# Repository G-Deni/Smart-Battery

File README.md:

# Smart-Battery
A battery standard used in all of my projects

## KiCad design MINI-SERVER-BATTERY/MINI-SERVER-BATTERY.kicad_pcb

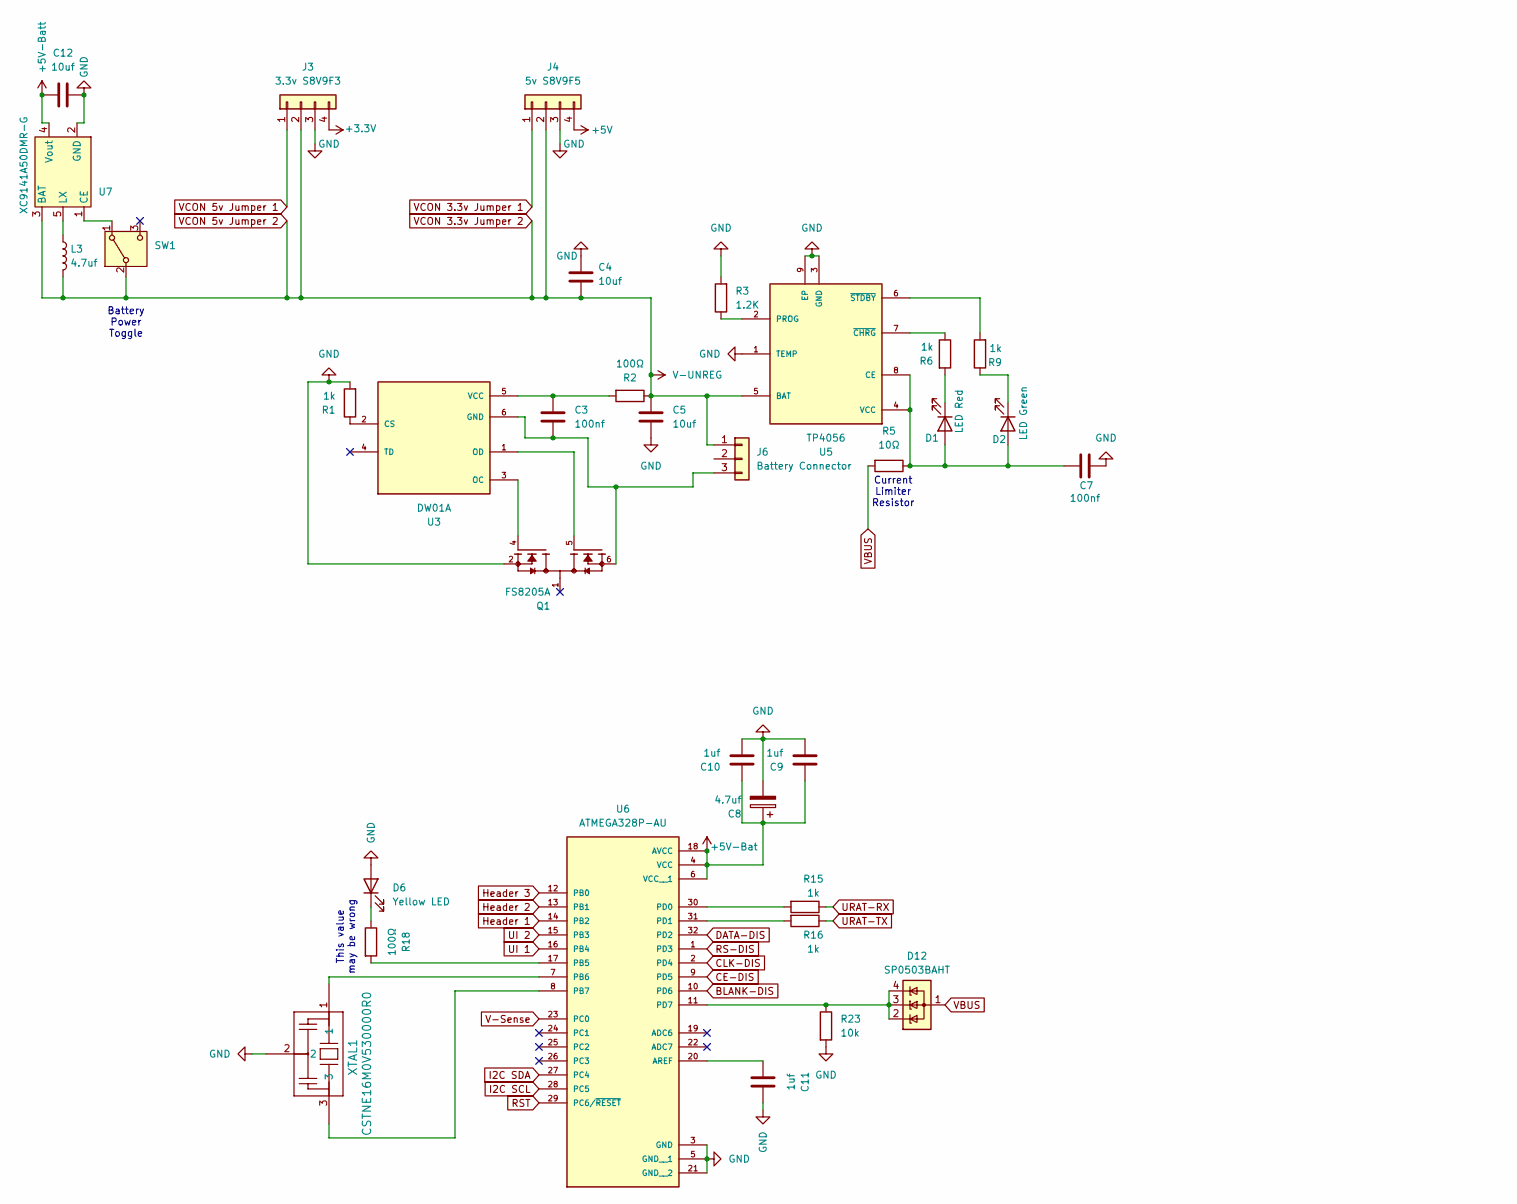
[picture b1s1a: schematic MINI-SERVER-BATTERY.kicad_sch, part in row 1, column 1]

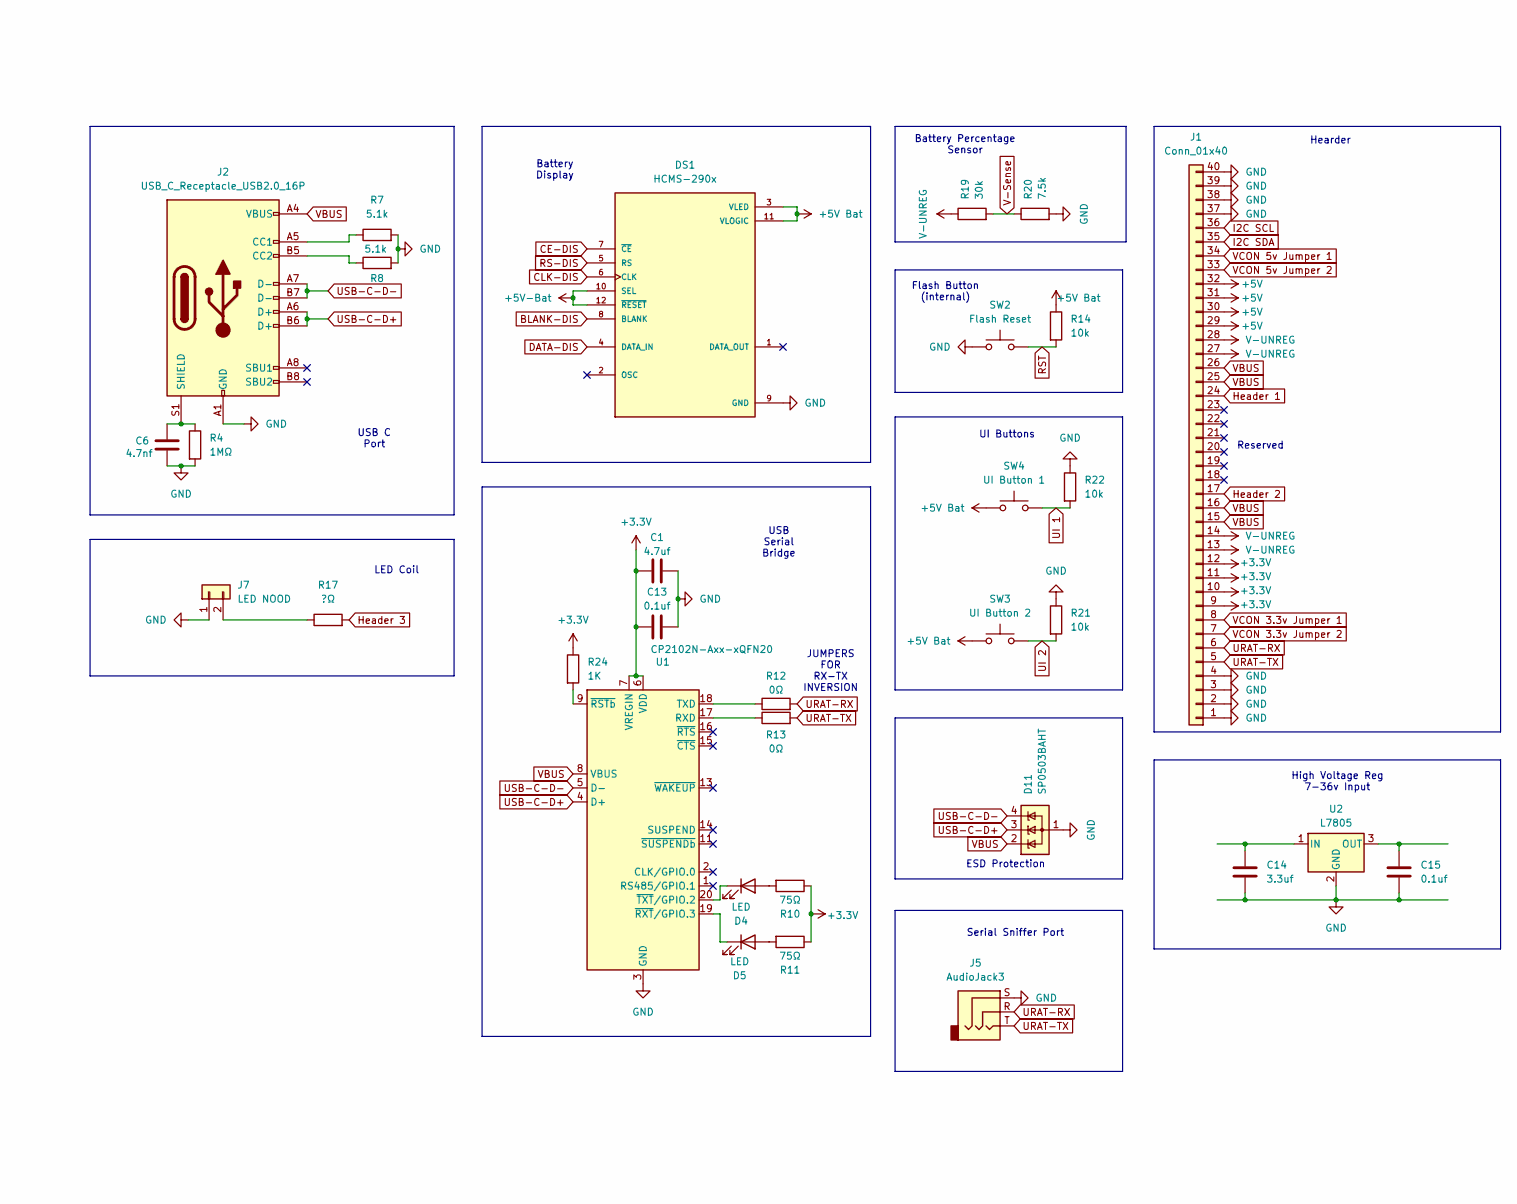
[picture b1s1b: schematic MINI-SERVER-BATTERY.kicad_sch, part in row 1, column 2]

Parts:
C1: 4.7uf; C_0603_1608Metric
C3, C7: 100nf; C_0603_1608Metric
C4, C5, C12: 10uf; C_0603_1608Metric
C6: 4.7nf; C_0603_1608Metric
C8: 4.7uf; C_0603_1608Metric_Pad1.08x0.95mm_HandSolder
C9, C10, C11: 1uf; C_0603_1608Metric_Pad1.08x0.95mm_HandSolder
C13, C15: 0.1uf; C_0603_1608Metric
C14: 3.3uf; C_0603_1608Metric
D1: LED Red; LED_0603_1608Metric
D2: LED Green; LED_0603_1608Metric
D4, D5: LED; LED_0603_1608Metric
D6: Yellow LED; LED_0805_2012Metric
D11, D12: SP0503BAHT; SOT-143
DS1: HCMS-290x; PARTREV N/A
J1: Conn_01x40; Samtec_MECF-20-0_-NP-L-DV_2x20_P1.27mm_Edge
J2: USB_C_Receptacle_USB2.0_16P; TYPE-C-31-M-12
J3: 3.3v S8V9F3; PinSocket_1x04_P2.54mm_Vertical
J4: 5v S8V9F5; PinSocket_1x04_P2.54mm_Vertical
J5: AudioJack3; Jack_3.5mm_CUI_SJ1-3513N_Horizontal
J6: Battery Connector; PinSocket_1x03_P2.54mm_Horizontal
J7: LED NOOD; PinSocket_1x02_P2.54mm_Vertical
L3: 4.7uf; INDPM5752X300N
Q1: FS8205A; SOT-23-6_Handsoldering; PARTREV 1.7
R1, R6, R9: 1k; R_0603_1608Metric
R2: 100Ω; R_0603_1608Metric
R3: 1.2K; R_0603_1608Metric
R4: 1MΩ; R_0603_1608Metric
R5: 10Ω; R_0603_1608Metric
R7, R8: 5.1k; R_0603_1608Metric
R10, R11: 75Ω; R_0603_1608Metric
R12, R13: 0Ω; R_0603_1608Metric
R14, R21, R22, R23: 10k; R_0603_1608Metric_Pad0.98x0.95mm_HandSolder
R15, R16: 1k; R_0603_1608Metric_Pad0.98x0.95mm_HandSolder
R17: ?Ω; R_0603_1608Metric
R18: 100Ω; R_0603_1608Metric_Pad0.98x0.95mm_HandSolder
R19: 30k; R_0603_1608Metric_Pad0.98x0.95mm_HandSolder
R20: 7.5k; R_0603_1608Metric_Pad0.98x0.95mm_HandSolder
R24: 1K; R_0603_1608Metric_Pad0.98x0.95mm_HandSolder
SW1: PCM12SMTR
SW2: Flash Reset; SW_Push_1P1T_NO_CK_KSC7xxJ
SW3: UI Button 2; Vertical Push Button 6_6
SW4: UI Button 1; Vertical Push Button 6_6
U1: CP2102N-Axx-xQFN20; SiliconLabs_QFN-20-1EP_3x3mm_P0.5mm_EP1.8x1.8mm
U2: L7805; TO-220-3_Horizontal_TabDown
U3: DW01A; SOT-23-6_Handsoldering; PARTREV 1.8
U5: TP4056
U6: ATMEGA328P-AU; TQFP-32_7x7mm_P0.8mm; PARTREV 8271A
U7: XC9141A50DMR-G; XC8107AC20MR-G
XTAL1: CSTNE16M0V530000R0

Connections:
+3.3V: C1.1, C13.1, J1.9, J1.10, J1.11, J1.12, J3.4, R10.1, R11.1, R24.1, U1.6 (VDD), U1.7 (VREGIN)
+5V: J1.29, J1.30, J1.31, J1.32, J4.4
+5V Bat: DS1.3 (VLED), DS1.11 (VLOGIC), R14.1, SW3.1, SW4.1
+5V-Bat: C8.1, C9.1, C10.1, DS1.10 (SEL), DS1.12 (~RESET), U6.4 (VCC), U6.6 (VCC__1), U6.18 (AVCC)
+5V-Batt: C12.1, U7.4 (Vout)
BLANK-DIS: DS1.8 (BLANK), U6.10 (PD6)
CE-DIS: DS1.7 (~CE), U6.9 (PD5)
CLK-DIS: DS1.6 (CLK), U6.2 (PD4)
DATA-DIS: DS1.4 (DATA_IN), U6.32 (PD2)
GND: C1.2, C4.2, C5.1, C6.2, C7.1, C8.2, C9.2, C10.2, C11.1, C12.2, C13.2, C14.2, C15.2, D6.2 (A), D11.1 (A), DS1.9 (GND), J1.1, J1.2, J1.3, J1.4, J1.37, J1.38, J1.39, J1.40, J2.A1 (GND), J2.A12 (GND), J2.B1 (GND), J2.B12 (GND), J3.3, J4.3, J5.S, J7.1, Q1.2, Q1.3, R1.2, R3.2, R4.2, R7.2, R8.2, R20.2, R21.1, R22.1, R23.2, SW2.1, U1.3 (GND), U1.12 (GND), U1.21 (GND), U2.2 (GND), U5.1 (TEMP), U5.3 (GND), U5.9 (EP), U6.3 (GND), U6.5 (GND__1), U6.21 (GND__2), U7.2 (GND), XTAL1.2
Header 1: J1.24, U6.14 (PB2)
Header 2: J1.17, U6.13 (PB1)
Header 3: R17.2, U6.12 (PB0)
I2C SCL: J1.36, U6.28 (PC5)
I2C SDA: J1.35, U6.27 (PC4)
unnamed: C7.2, D1.2 (A), D2.2 (A), R5.1, U5.4 (VCC), U5.8 (CE)
unnamed: D1.1 (K), R6.2
unnamed: D2.1 (K), R9.1
unnamed: D4.2 (A), R10.2
unnamed: D4.1 (K), U1.20 (~TXT/GPIO.2)
unnamed: D5.2 (A), R11.2
unnamed: D5.1 (K), U1.19 (~RXT/GPIO.3)
unnamed: D6.1 (K), R18.1
unnamed: J2.A5 (CC1), R7.1
unnamed: J2.B5 (CC2), R8.1
unnamed: C6.1, J2.S1 (SHIELD), R4.1
unnamed: C3.1, J6.3, Q1.6, Q1.7, U3.6 (GND)
unnamed: J7.2, R17.1
unnamed: SW1.1 (A), U7.1 (CE)
unnamed: R13.1, U1.17 (RXD)
unnamed: R12.1, U1.18 (TXD)
unnamed: R24.2, U1.9 (~RSTb)
unnamed: C14.1, U2.1 (IN)
unnamed: C15.1, U2.3 (OUT)
unnamed: R1.1, U3.2 (CS)
unnamed: Q1.4, U3.3 (OC)
unnamed: Q1.5, U3.1 (OD)
unnamed: C3.2, R2.2, U3.5 (VCC)
unnamed: R3.1, U5.2 (PROG)
unnamed: R6.1, U5.7 (~CHRG)
unnamed: R9.2, U5.6 (~STDBY)
unnamed: C11.2, U6.20 (AREF)
unnamed: R18.2, U6.17 (PB5)
unnamed: U6.7 (PB6), XTAL1.1
unnamed: U6.8 (PB7), XTAL1.3
unnamed: R15.2, U6.30 (PD0)
unnamed: R16.2, U6.31 (PD1)
unnamed: D12.2 (K), D12.3 (K), D12.4 (K), R23.1, U6.11 (PD7)
unnamed: L3.1, U7.5 (LX)
RS-DIS: DS1.5 (RS), U6.1 (PD3)
RST: R14.2, SW2.2, U6.29 (PC6/~RESET)
UI 1: R22.2, SW4.2, U6.16 (PB4)
UI 2: R21.2, SW3.2, U6.15 (PB3)
URAT-RX: J1.6, J5.R, R12.2, R15.1
URAT-TX: J1.5, J5.T, R13.2, R16.1
USB-C-D+: D11.3 (K), J2.A6 (D+), J2.B6 (D+), U1.4 (D+)
USB-C-D-: D11.4 (K), J2.A7 (D-), J2.B7 (D-), U1.5 (D-)
V-Sense: R19.2, R20.1, U6.23 (PC0)
VBUS: D11.2 (K), D12.1 (A), J1.15, J1.16, J1.25, J1.26, J2.A4 (VBUS), J2.A9 (VBUS), J2.B4 (VBUS), J2.B9 (VBUS), R5.2, U1.8 (VBUS)
VCON 5v Jumper 1: J1.34, J3.1
VCON 3.3v Jumper 1: J1.8, J4.1
VCON 3.3v Jumper 2: C4.1, C5.2, J1.7, J1.13, J1.14, J1.27, J1.28, J1.33, J3.2, J4.2, J6.1, L3.2, R2.1, R19.1, SW1.2 (B), U5.5 (BAT), U7.3 (BAT)

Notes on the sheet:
Flash Button (internal)
Reserved
This value may be wrong
Serial Sniffer Port
Battery Display
High Voltage Reg 7-36v Input
UI Buttons
ESD Protection
Current Limiter Resistor
LED Coil
Battery Power Toggle
USB Serial Bridge
USB C Port
Battery Percentage Sensor
Hearder
JUMPERS FOR RX-TX INVERSION

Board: 2 copper layers, 66 parts (2 on the bottom side), 62 nets, no tracks yet.

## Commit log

2024-12-22 - added project from the mini server repo
2024-12-24 -added firmware (it's not nearly done)
2025-01-13 - added voltage divider to firmware
